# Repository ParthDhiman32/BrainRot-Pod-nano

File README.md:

# BrainRot-Pod-nano
BrainRot Pod Nano is an overengineered Embedded system project wth complex PCB and beautiful CAD enclosure mainly made for playing meme sounds and also can work as a mini music player   

# Motivation to create this and Outline of features
okay so this sounds like a really dumb project but the thing is this is a really good project infact this project will help me sharpen my PCB and CAD skills to a even newer level Because i will try my best to Make this project as polished as possible like i want to make this project as perfect as it could be 
I wanted to make a project to see what level are my skills are at.

My goals for this project are to mainly have a Beauitiful! PCB which is really pleasing to an engineers eyes and to also design an enclosure which encapsulates the beauty of the PCB while itself mantaining a really Smooth Sleek and Matte design 

This project will have a shitload of features ranging from a rotatory encoder to adjust the volume to a SD card module to load your songs to and even a AUX Jack because..WHY NOT!!! 

I want to mantain a sleek design like how apple iPODs used to be like and also make my own UI and UX for this project and Many tactile buttons for feedback maybe i'll even add a vibrating motor for haptic feedback

# Main Components Used:
1.  ESP32-S3-WROOM-1 Module 
2.  PCM5102A - Audio DAC
3.  MAX98357A - Audio Amplifer 
4.  TP4056 - Li-Po charger IC 
5.  DW01A - Battery Protection IC 
6.  FS83205A - Power Mosfet 
7.  ME6211 - LDO Regulator 
8.  AO3400 - BacLight Switch for TFT 
9.  1.54" SPI TFT display
10. Li-Po battery - 1100mAh 3.7V
11. Speaker - 3W 4Ω dynamic speaker
12. Rotary Encoder SMD
13. Tactile Buttons SMD 
14. USB C connector - 16 pin tactile receptacle 
15. Audio Jack - PJ-320A 3.5mm Stereo Audio Jack
16. SD Card slot - Push Pull SD card slot 
17. Battry connector - JST battery connector 
18. A lot of passive resistors 
19. A lot of passive capacitors 
20. M2 screws 

## Reason for selection of each part 
 1. ESP32-S3-WROOM-1 Module - this specific module was selected because it has 8MB of PSRAM which acts as the DMA audio buffer also because it has more than enough processing power and as it also has wifi and bluetooth i can add these features later to my project 

 2. PCM5102A - Normally audio DACs require bulky DC blocking Capacitors but as this IC has a negative voltage rail which produces ground centered Audio this eliminates the need of those bulky DC Blosking capacitors 

 3. MAX93857A - this is an Mono Class-D audio amplifer IC (amp for short) and it shares the common I2C bus as the DAC and also it will shut off automatically when the Audio jack / AUX will be connected 

 4. TP4056 - This is a very common Typical Li-Po battery chargin IC no need for more explanation

 5. DW01A - This is a battery protection IC which is paired with TP4056 which provides Short Circuit and overload protection to the battery 

 6. AP2112K-3.3 - This is a ultra low dropout power regulator meaning it will extract maximum voltage from the Lipo battery before it drops out it drops out around 3.55V unlike older inefficient AMS117 which dropout at around 4.3V

 7. ME6211 - efficiently converts the 5V from the power system to 3V3 volts the entire circuitry works on

 8. AO3400 - This is a simple PWM switch which will be used to control the intensity of Backlight of the 2.8" TFT Display 

 9.  1.54" SPI TFT display - Very high quality display with vivid range of colours and no grainy text 

 10. 1100mAh Li-Po battery provied long enough battery life that if optmized could give all day long runtime 
 
 11. 3W 4Ω dynamic speaker - Loud enough speaker and also can be driven Efficiently by our Audio amplifier circuitry 

 12. Rotary Encoder - To simply control the Volume 

 13. Tactile Buttons - Buttons with 5-20N of actuation force so that it gives a premium click! feel 

 14. USB C connector - for charging the battery and flashing / Updating the firmware 

 15. Audio Jack - Only to connect external wired earphones

 16. SD Card slot - Ti store Songs / MEME sounds 

 17. Battery Connector - A JST batter connector to prevent accidental rever polatiy connections 

 18. 19.  resistors and capacitors - Do i even need to explain why this is needed 

 20. M2 screws are small enough to be screwed and not be noticed easily

# PCB Schematics

## Complete Schematic

---

## Complete PCB

### Op-Amps & Audio Circuit

---

## Power System

---

## ESP32 & Peripheral Connections

# CAD DESIGN 

# BOM

| # | Component | Qty | Estimated Unit Cost | Estimated Total |
|---|---|---:|---:|---:|
| 1 | ESP32-S3-WROOM-1, 8MB PSRAM | 1 | $3.70 | $3.70 |
| 2 | PCM5102A Audio DAC | 1 | $1.25 | $1.25 |
| 3 | MAX98357A Class-D Audio Amplifier | 1 | $1.05 | $1.05 |
| 4 | TP4056 Li-Po Charger IC | 1 | $0.16 | $0.16 |
| 5 | DW01A Battery Protection IC | 1 | $0.11 | $0.11 |
| 6 | FS8205A / FS83205A Battery Protection MOSFET | 1 | $0.11 | $0.11 |
| 7 | ME6211 / AP2112K 3.3V LDO | 1 | $0.16 | $0.16 |
| 8 | AO3400 Backlight MOSFET | 1 | $0.08 | $0.08 |
| 9 | 1.54" SPI TFT Display | 1 | $2.63 | $2.63 |
| 10 | 3.7V 1100mAh Li-Po Battery | 1 | $3.15 | $3.15 |
| 11 | 3W 4Ω Dynamic Speaker | 1 | $1.05 | $1.05 |
| 12 | SMD Rotary Encoder | 1 | $0.42 | $0.42 |
| 13 | SMD Tactile Buttons | ~6 | $0.05 | $0.32 |
| 14 | USB-C 16-Pin Receptacle | 1 | $0.21 | $0.21 |
| 15 | PJ-320A 3.5mm Stereo Audio Jack | 1 | $0.21 | $0.21 |
| 16 | Push-Pull SD Card Socket | 1 | $0.42 | $0.42 |
| 17 | JST Battery Connector | 1 | $0.16 | $0.16 |
| 18 | Resistors | ~20–30 | — | $0.32 |
| 19 | Capacitors | ~20–30 | — | $0.63 |
| 20 | Misc. Diodes / LEDs / Small Components | — | — | $0.32 |
| 21 | M2 Screws + Mechanical Hardware | — | — | $0.53 |
| | **TOTAL ROUGH BOM ESTIMATE** | | | **≈ $17.01** |
| | **Recommended Budget Range** | | | **$17–$20** |

> **Note:** This is a rough prototype estimate. Actual prices may vary depending on the supplier, exact MPNs, quantity, shipping, and taxes. PCB manufacturing, assembly, and 3D-printing costs are **not included**.

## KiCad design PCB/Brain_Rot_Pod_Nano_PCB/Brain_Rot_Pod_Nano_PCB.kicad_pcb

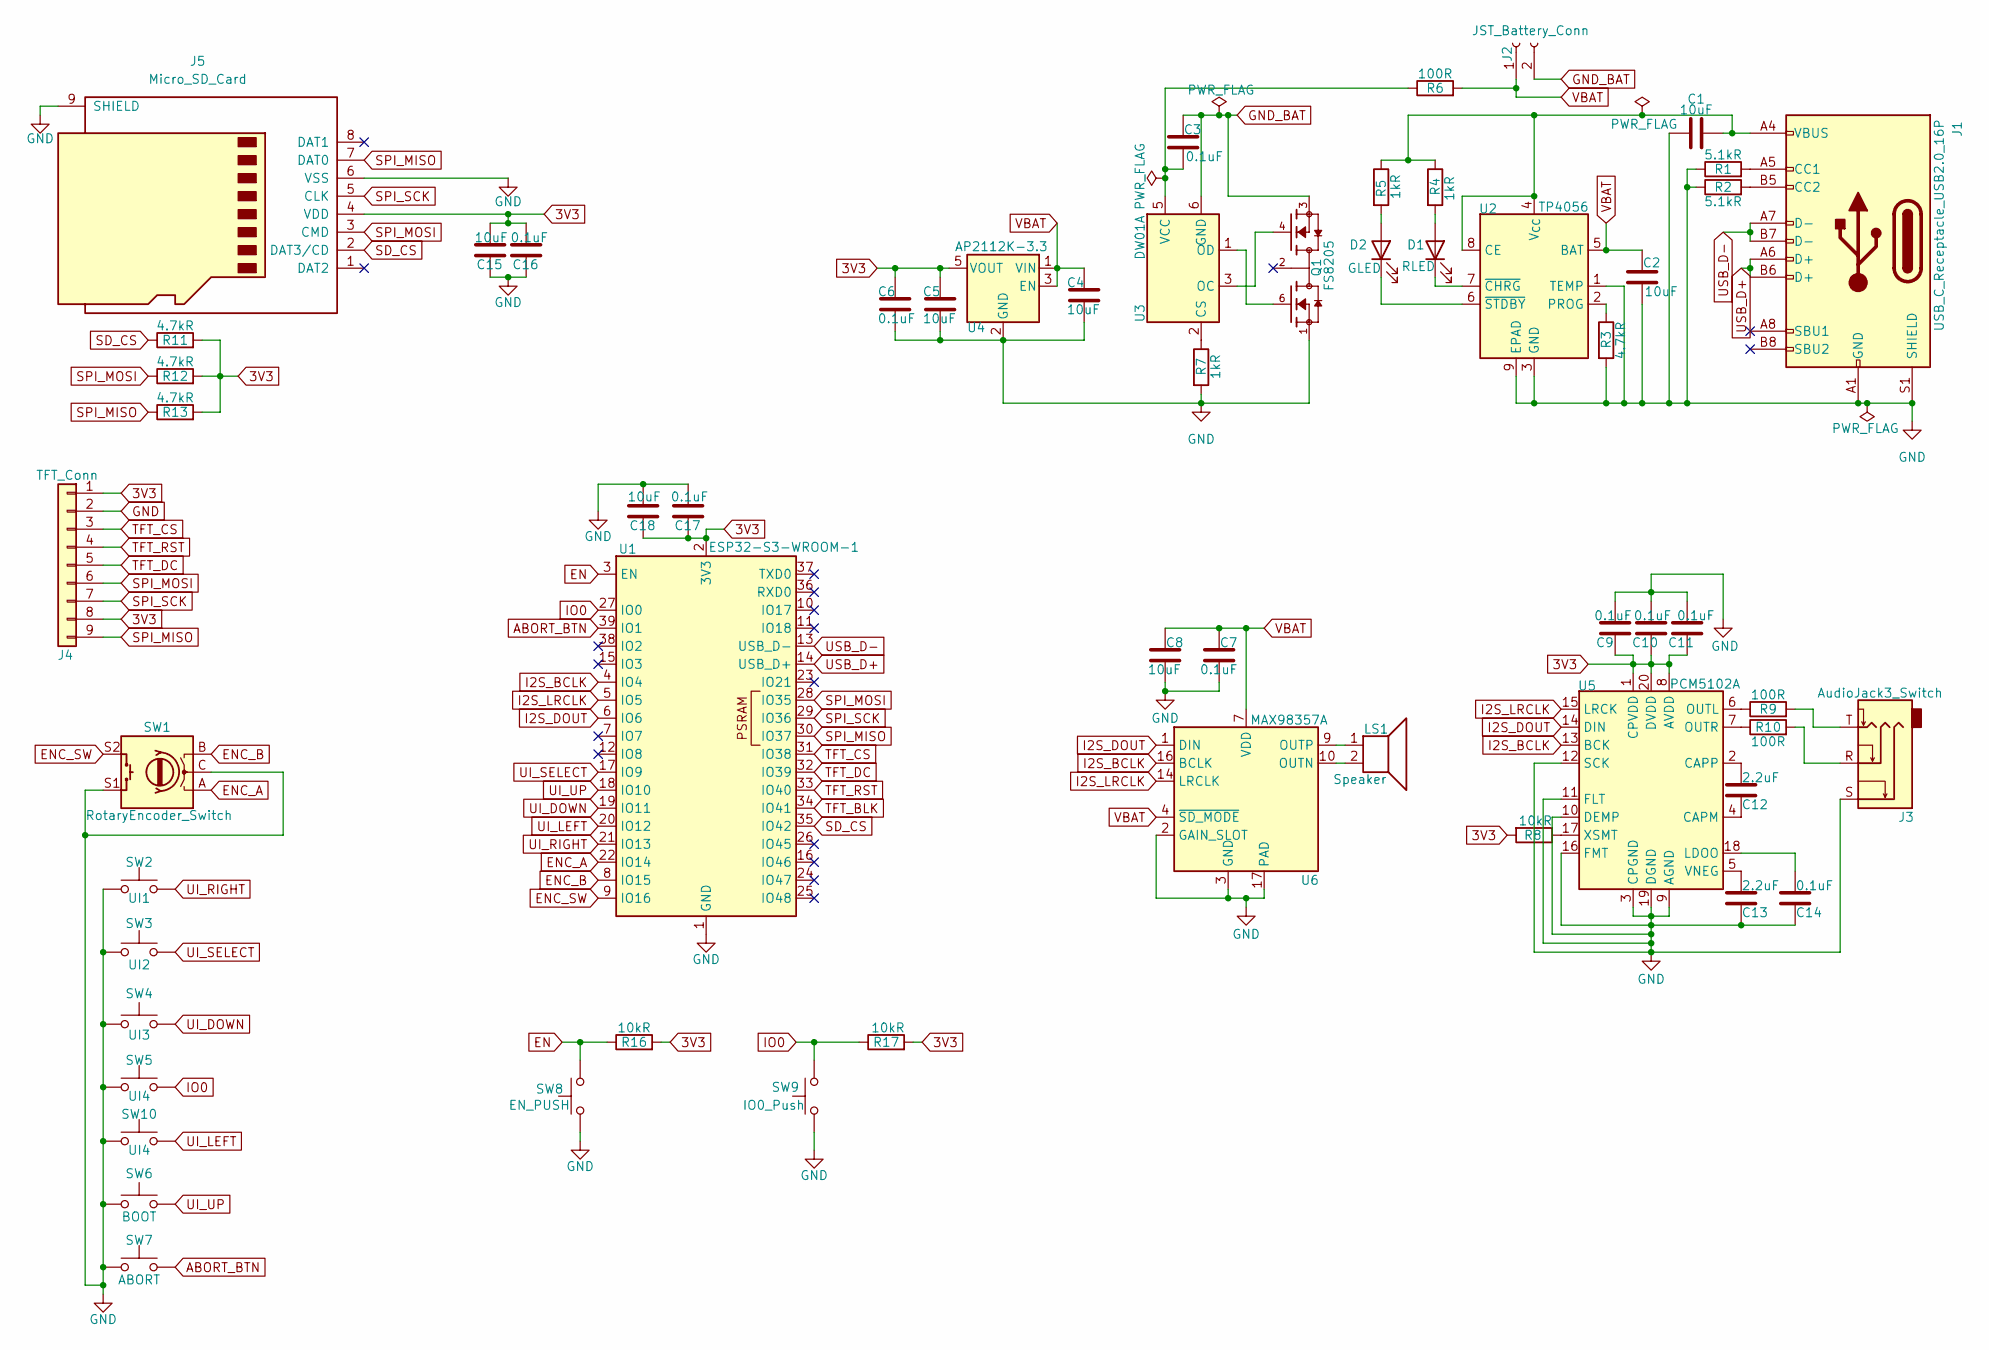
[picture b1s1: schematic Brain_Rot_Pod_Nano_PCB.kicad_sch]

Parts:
C1, C2, C4, C5, C8, C15, C18: 10uF; C_0805_2012Metric
C3, C6, C7, C9, C10, C11, C14, C16, C17: 0.1uF; C_0805_2012Metric
C12, C13: 2.2uF; C_0805_2012Metric
D1: RLED; LED_0805_2012Metric
D2: GLED; LED_0805_2012Metric
J1: USB_C_Receptacle_USB2.0_16P; USB_C_Receptacle_HRO_TYPE-C-31-M-12
J2: JST_Battery_Conn; JST_PH_S2B-PH-K_1x02_P2.00mm_Horizontal
J3: AudioJack3_Switch; Jack_3.5mm_CUI_SJ1-3523N_Horizontal
J4: TFT_Conn; PinHeader_1x09_P2.54mm_Vertical
J5: Micro_SD_Card; microSD_HC_Hirose_DM3AT-SF-PEJM5
LS1: Speaker; JST_PH_S2B-PH-K_1x02_P2.00mm_Horizontal
Q1: FS8205; TSSOP-8_4.4x3mm_P0.65mm; PARTREV 1.9
R1, R2: 5.1kR; R_0805_2012Metric
R3, R11, R12, R13: 4.7kR; R_0805_2012Metric
R4, R5, R7: 1kR; R_0805_2012Metric
R6, R9, R10: 100R; R_0805_2012Metric
R8, R16, R17: 10kR; R_0805_2012Metric
SW1: RotaryEncoder_Switch; RotaryEncoder_Alps_EC11E-Switch_Vertical_H20mm
SW2: UI1; SW_Cherry_MX_1.00u_PCB
SW3: UI2; SW_Cherry_MX_1.00u_PCB
SW4: UI3; SW_Cherry_MX_1.00u_PCB
SW5, SW10: UI4; SW_Cherry_MX_1.00u_PCB
SW6: BOOT; SW_Cherry_MX_1.00u_PCB
SW7: ABORT; SW_Cherry_MX_1.00u_PCB
SW8: EN_PUSH; SW_PUSH-12mm
SW9: IO0_Push; SW_PUSH-12mm
U1: ESP32-S3-WROOM-1
U2: TP4056; SOIC-8-1EP_3.9x4.9mm_P1.27mm_EP2.41x3.3mm_ThermalVias
U3: DW01A; SOT-23-6
U4: AP2112K-3.3; SOT-23-5
U5: PCM5102A; TSSOP-20_4.4x6.5mm_P0.65mm
U6: MAX98357A; TQFN-16-1EP_3x3mm_P0.5mm_EP1.23x1.23mm

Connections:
3V3: C5.1, C6.1, C9.2, C10.2, C11.2, C15.1, C16.1, C17.2, C18.2, J4.1, J4.8, J5.4 (VDD), R8.2, R11.2, R12.2, R13.2, R16.2, R17.2, U1.2 (3V3), U4.5 (VOUT), U5.1 (CPVDD), U5.8 (AVDD), U5.20 (DVDD)
ABORT_BTN: SW7.2, U1.39 (IO1)
EN: R16.1, SW8.2, U1.3 (EN)
ENC_A: SW1.A, U1.22 (IO14)
ENC_B: SW1.B, U1.8 (IO15)
ENC_SW: SW1.S2, U1.9 (IO16)
GND: C1.1, C2.1, C4.2, C5.2, C6.2, C7.2, C8.2, C9.1, C10.1, C11.1, C13.2, C14.2, C15.2, C16.2, C17.1, C18.1, J1.A1 (GND), J1.A12 (GND), J1.B1 (GND), J1.B12 (GND), J1.S1 (SHIELD), J3.S, J4.2, J5.6 (VSS), J5.9 (SHIELD), Q1.1, R1.1, R2.1, R3.2, R7.2, SW1.C, SW1.S1, SW2.1, SW3.1, SW4.1, SW5.1, SW6.1, SW7.1, SW8.1, SW9.1, SW10.1, U1.1 (GND), U1.40 (GND), U1.41 (GND), U2.1 (TEMP), U2.3 (GND), U2.9 (EPAD), U4.2 (GND), U5.3 (CPGND), U5.9 (AGND), U5.10 (DEMP), U5.11 (FLT), U5.12 (SCK), U5.16 (FMT), U5.19 (DGND), U6.2 (GAIN_SLOT), U6.3 (GND), U6.11 (GND), U6.15 (GND), U6.17 (PAD)
GND_BAT: C3.1, J2.2, Q1.3, U3.6 (GND)
I2S_BCLK: U1.4 (IO4), U5.13 (BCK), U6.16 (BCLK)
I2S_DOUT: U1.6 (IO6), U5.14 (DIN), U6.1 (DIN)
I2S_LRCLK: U1.5 (IO5), U5.15 (LRCK), U6.14 (LRCLK)
IO0: R17.1, SW5.2, SW9.2, U1.27 (IO0)
unnamed: D1.2 (A), R4.2
unnamed: D1.1 (K), U2.7 (~CHRG)
unnamed: D2.2 (A), R5.2
unnamed: D2.1 (K), U2.6 (~STDBY)
unnamed: J1.A5 (CC1), R1.2
unnamed: J1.B5 (CC2), R2.2
unnamed: J3.R, R10.2
unnamed: J3.T, R9.2
unnamed: C1.2, J1.A4 (VBUS), J1.A9 (VBUS), J1.B4 (VBUS), J1.B9 (VBUS), R4.1, R5.1, U2.4 (V_{CC}), U2.8 (CE)
unnamed: R3.1, U2.2 (PROG)
unnamed: R7.1, U3.2 (CS)
unnamed: Q1.4, U3.3 (OC)
unnamed: Q1.6, U3.1 (OD)
unnamed: C3.2, R6.1, U3.5 (VCC)
unnamed: C12.2, U5.4 (CAPM)
unnamed: C12.1, U5.2 (CAPP)
unnamed: C14.1, U5.18 (LDOO)
unnamed: R9.1, U5.6 (OUTL)
unnamed: R10.1, U5.7 (OUTR)
unnamed: C13.1, U5.5 (VNEG)
unnamed: R8.1, U5.17 (XSMT)
unnamed: LS1.2, U6.10 (OUTN)
unnamed: LS1.1, U6.9 (OUTP)
SD_CS: J5.2 (DAT3/CD), R11.1, U1.35 (IO42)
SPI_MISO: J4.9, J5.7 (DAT0), R13.1, U1.30 (IO37)
SPI_MOSI: J4.6, J5.3 (CMD), R12.1, U1.28 (IO35)
SPI_SCK: J4.7, J5.5 (CLK), U1.29 (IO36)
TFT_BLK: U1.34 (IO41)
TFT_CS: J4.3, U1.31 (IO38)
TFT_DC: J4.5, U1.32 (IO39)
TFT_RST: J4.4, U1.33 (IO40)
UI_DOWN: SW4.2, U1.19 (IO11)
UI_LEFT: SW10.2, U1.20 (IO12)
UI_RIGHT: SW2.2, U1.21 (IO13)
UI_SELECT: SW3.2, U1.17 (IO9)
UI_UP: SW6.2, U1.18 (IO10)
USB_D+: J1.A6 (D+), J1.B6 (D+), U1.14 (USB_D+)
USB_D-: J1.A7 (D-), J1.B7 (D-), U1.13 (USB_D-)
VBAT: C2.2, C4.1, C7.1, C8.1, J2.1, R6.2, U2.5 (BAT), U4.1 (VIN), U4.3 (EN), U6.4 (~SD_MODE), U6.7 (VDD), U6.8 (VDD)

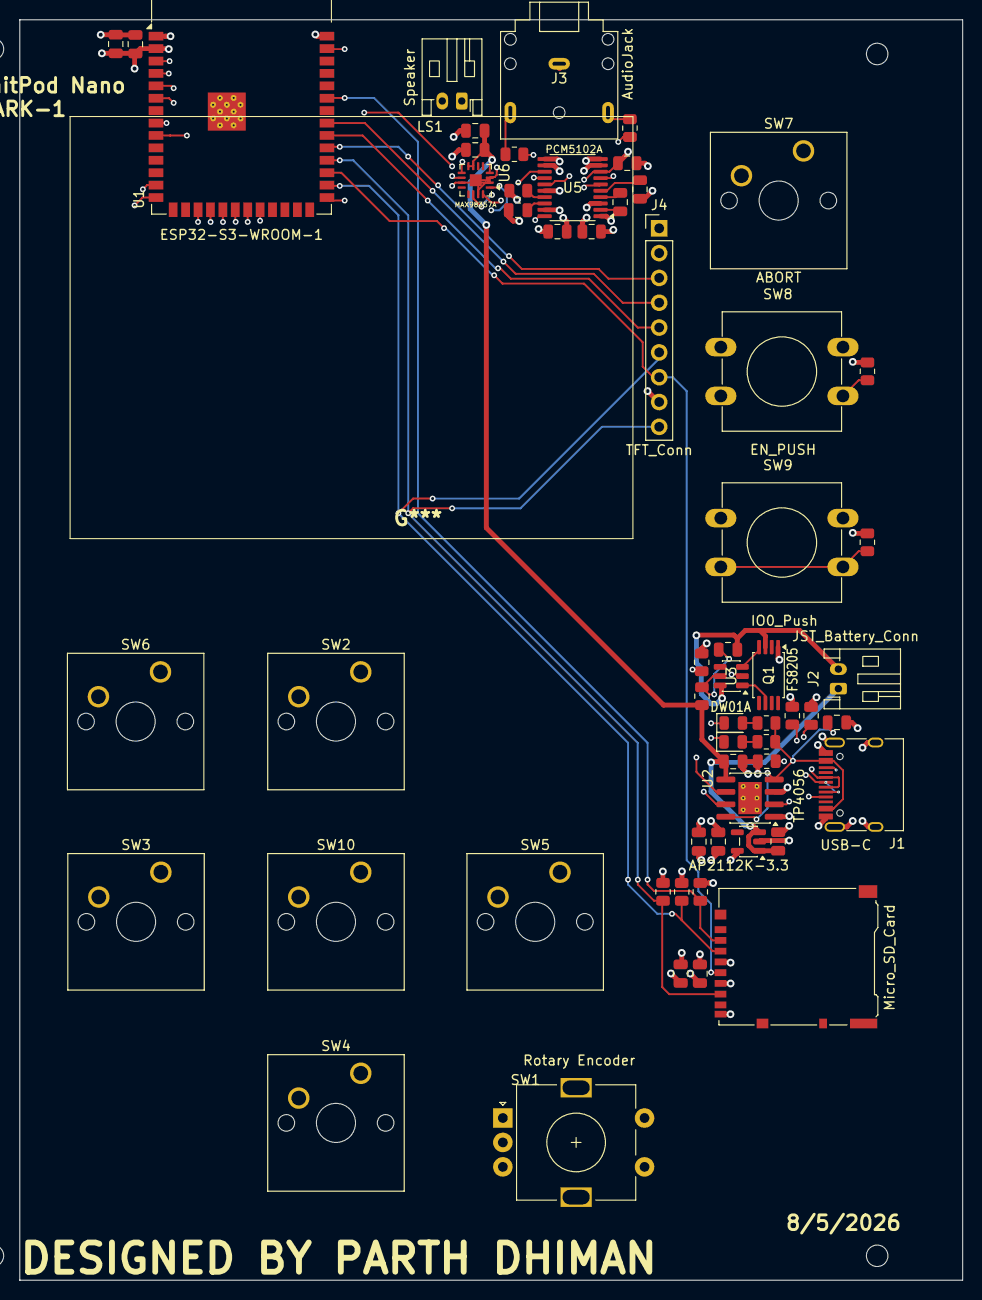
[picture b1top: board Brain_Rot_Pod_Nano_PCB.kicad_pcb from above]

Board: 6 copper layers, 96.5 x 129.0 mm, 58 parts (0 on the bottom side), 50 nets.

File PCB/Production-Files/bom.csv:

Designator,Footprint,Quantity,Value,LCSC Part #
"C1, C15, C18, C2, C4, C5, C8",0805,7,10uF,
"C10, C11, C14, C16, C17, C3, C6, C7, C9",0805,9,0.1uF,
"C12, C13",0805,2,2.2uF,
D1,0805,1,RLED,
D2,0805,1,GLED,
J1,USB_C_Receptacle_HRO_TYPE-C-31-M-12,1,USB-C,
J2,JST_PH_S2B-PH-K_1x02_P2.00mm_Horizontal,1,JST_Battery_Conn,
J3,Jack_3.5mm_CUI_SJ1-3523N_Horizontal,1,AudioJack,
J4,PinHeader_1x09_P2.54mm_Vertical,1,TFT_Conn,
J5,microSD_HC_Hirose_DM3AT-SF-PEJM5,1,Micro_SD_Card,
LS1,JST_PH_S2B-PH-K_1x02_P2.00mm_Horizontal,1,Speaker,
Q1,TSSOP-8_4.4x3mm_P0.65mm,1,FS8205,
"R1, R2",0805,2,5.1kR,
"R10, R6, R9",0805,3,100R,
"R11, R12, R13, R3",0805,4,4.7kR,
"R16, R17, R8",0805,3,10kR,
"R4, R5, R7",0805,3,1kR,
SW1,RotaryEncoder_Alps_EC11E-Switch_Vertical_H20mm,1,Rotary Encoder,
"SW10, SW5",SW_Cherry_MX_1.00u_PCB,2,UI4,
SW2,SW_Cherry_MX_1.00u_PCB,1,UI1,
SW3,SW_Cherry_MX_1.00u_PCB,1,UI2,
SW4,SW_Cherry_MX_1.00u_PCB,1,UI3,
SW6,SW_Cherry_MX_1.00u_PCB,1,BOOT,
SW7,SW_Cherry_MX_1.00u_PCB,1,ABORT,
SW8,SW_PUSH-12mm,1,EN_PUSH,
SW9,SW_PUSH-12mm,1,IO0_Push,
U1,ESP32-S3-WROOM-1,1,ESP32-S3-WROOM-1,
U2,SOIC-8-1EP_3.9x4.9mm_P1.27mm_EP2.41x3.3mm_ThermalVias,1,TP4056,
U3,SOT-23-6,1,DW01A,
U4,SOT-23-5,1,AP2112K-3.3,
U5,TSSOP-20_4.4x6.5mm_P0.65mm,1,PCM5102A,
U6,TQFN-16-1EP_3x3mm_P0.5mm_EP1.23x1.23mm,1,MAX98357A,

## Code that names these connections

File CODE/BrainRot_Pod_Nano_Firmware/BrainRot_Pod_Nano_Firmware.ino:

// Sample firmware for Brain_Rot_Pod_Nano
// Overengineered Firmware for Overengineered project

#include <SPI.h>
#include <SD.h>
#include <TFT_eSPI.h>
#include "AudioFileSourceSD.h"
#include "AudioGeneratorWAV.h"
#include "AudioOutputI2S.h"

#define I2S_BCLK       4
#define I2S_LRC        5
#define I2S_DOUT       6

#define SD_CS          42
#define SD_MOSI        35
#define SD_MISO        37
#define SD_CLK         36

#define ENC_A          14
#define ENC_B          15
#define ENC_SW         16

#define BTN_ABORT      1

enum SystemState {
  STATE_MENU,
  STATE_MUSIC_PLAYING,
  STATE_MEME_SETUP,
  STATE_MEME_ARMED,
  STATE_MEME_PLAYING
};

SystemState currentState = STATE_MENU;

AudioGeneratorWAV *wav;
AudioFileSourceSD *file;
AudioOutputI2S *out;

float currentVolume = 0.6;

uint32_t memeStartTime = 0;
uint32_t memeDelayMs = 60000;
bool memeArmed = false;

uint32_t lastButtonPress = 0;
int lastEncoderState = HIGH;

uint32_t lastUIUpdate = 0;
bool uiNeedsUpdate = true;

TFT_eSPI tft = TFT_eSPI();

void setup() {

  Serial.begin(115200);

  pinMode(ENC_A, INPUT_PULLUP);
  pinMode(ENC_B, INPUT_PULLUP);
  pinMode(ENC_SW, INPUT_PULLUP);

  pinMode(BTN_ABORT, INPUT_PULLUP);

  // Initialize TFT
  tft.init();
  tft.setRotation(1);
  tft.fillScreen(TFT_BLACK);
  tft.setTextColor(TFT_WHITE, TFT_BLACK);

  // Initialize SPI
  SPI.begin(SD_CLK, SD_MISO, SD_MOSI, SD_CS);

  // Initialize SD card
  if (!SD.begin(SD_CS, SPI, 40000000)) {

    tft.drawString("SD CARD FAILED", 10, 10, 2);

    while (1) {
      delay(100);
    }
  }

  // Initialize audio system
  audioLogger = &Serial;

  file = new AudioFileSourceSD();
  out = new AudioOutputI2S();
  wav = new AudioGeneratorWAV();

  // Configure I2S
  out->SetPinout(I2S_BCLK, I2S_LRC, I2S_DOUT);

  // Set initial volume
  out->SetGain(currentVolume);

  uiNeedsUpdate = true;
}


void loop() {

  handleInputs();
  handleAudio();
  handleMemeTimer();
  updateUI();

}


void handleAudio() {

  if (wav && wav->isRunning()) {

    if (!wav->loop()) {

      wav->stop();

      file->close();

      if (currentState == STATE_MEME_PLAYING) {

        currentState = STATE_MENU;
        uiNeedsUpdate = true;

      }
    }
  }
}


void playFile(const char *filename) {

  if (wav->isRunning()) {

    wav->stop();
    file->close();

  }

  if (!file->open(filename)) {

    Serial.print("Failed to open: ");
    Serial.println(filename);

    currentState = STATE_MENU;
    uiNeedsUpdate = true;

    return;
  }

  if (!wav->begin(file, out)) {

    Serial.println("Failed to start WAV playback");

    file->close();

    currentState = STATE_MENU;
    uiNeedsUpdate = true;

    return;
  }
}


void handleInputs() {

  uint32_t now = millis();

  // Button handling
  if (now - lastButtonPress > 50) {

    // Encoder push button
    if (digitalRead(ENC_SW) == LOW) {

      if (currentState == STATE_MUSIC_PLAYING) {

        // Mute / unmute audio
        if (wav->isRunning()) {

          if (currentVolume > 0.0) {
            out->SetGain(0.0);
          }
          else {
            out->SetGain(0.6);
          }

        }

      }

      else if (currentState == STATE_MEME_SETUP) {

        memeArmed = true;
        memeStartTime = now;

        currentState = STATE_MEME_ARMED;

        uiNeedsUpdate = true;

      }

      else if (currentState == STATE_MENU) {

        playFile("/music/song.wav");

        currentState = STATE_MUSIC_PLAYING;

        uiNeedsUpdate = true;

      }

      lastButtonPress = now;
    }


    // Abort button
    if (digitalRead(BTN_ABORT) == LOW) {

      if (wav->isRunning()) {
        wav->stop();
      }

      if (file) {
        file->close();
      }

      memeArmed = false;

      currentState = STATE_MENU;

      uiNeedsUpdate = true;

      lastButtonPress = now;
    }
  }


  // Rotary encoder
  int currentEncoderState = digitalRead(ENC_A);

  if (currentEncoderState != lastEncoderState &&
      currentEncoderState == LOW) {

    if (digitalRead(ENC_B) != currentEncoderState) {

      currentVolume += 0.05;

      if (currentVolume > 1.0) {
        currentVolume = 1.0;
      }

    }
    else {

      currentVolume -= 0.05;

      if (currentVolume < 0.0) {
        currentVolume = 0.0;
      }
    }

    out->SetGain(currentVolume);

    uiNeedsUpdate = true;
  }

  lastEncoderState = currentEncoderState;
}


void handleMemeTimer() {

  if (currentState == STATE_MEME_ARMED && memeArmed) {

    uint32_t now = millis();

    uint32_t elapsed = now - memeStartTime;


    // Update countdown once per second
    if (now - lastUIUpdate >= 1000) {

      uiNeedsUpdate = true;
      lastUIUpdate = now;

    }


    // Timer expired
    if (elapsed >= memeDelayMs) {

      memeArmed = false;

      currentState = STATE_MEME_PLAYING;

      uiNeedsUpdate = true;

      playFile("/memes/faaaah.wav");
    }
  }
}


void updateUI() {

  if (!uiNeedsUpdate) {
    return;
  }

  uiNeedsUpdate = false;

  tft.fillScreen(TFT_BLACK);


  switch (currentState) {

    case STATE_MENU:

      tft.drawString("BRAINROT POD NANO", 10, 10, 4);

      tft.drawString("> MUSIC", 10, 50, 2);

      tft.drawString("  MEME SETUP", 10, 70, 2);

      break;


    case STATE_MUSIC_PLAYING:

      tft.drawString("MUSIC PLAYING", 10, 10, 4);

      tft.drawString("> song.wav", 10, 50, 2);

      tft.drawString("Volume:", 10, 90, 2);

      tft.drawNumber(
        (int)(currentVolume * 100),
        80,
        90,
        2
      );

      break;


    case STATE_MEME_SETUP:

      tft.drawString("MEME SETUP", 10, 10, 4);

      tft.drawString("FAAAAAH.wav", 10, 50, 2);

      tft.drawString("Delay:", 10, 80, 2);

      tft.drawNumber(
        memeDelayMs / 1000,
        80,
        80,
        2
      );

      tft.drawString("SECONDS", 120, 80, 2);

      break;


    case STATE_MEME_ARMED: {

      tft.drawString("MEME TIMER", 10, 10, 4);

      tft.drawString("FAAAAAH.wav", 10, 40, 2);

      uint32_t elapsed = millis() - memeStartTime;

      uint32_t remainingMs = 0;

      if (elapsed < memeDelayMs) {
        remainingMs = memeDelayMs - elapsed;
      }

      uint32_t remaining = remainingMs / 1000;

      tft.drawString("T-MINUS:", 10, 80, 4);

      tft.drawNumber(
        remaining,
        120,
        80,
        4
      );

      break;
    }


    case STATE_MEME_PLAYING:

      tft.fillScreen(TFT_RED);

      tft.setTextColor(TFT_WHITE, TFT_RED);

      tft.drawString("💀", 40, 50, 4);
      tft.drawString("FAAAAAAH", 40, 100, 4);

      tft.setTextColor(TFT_WHITE, TFT_BLACK);

      break;
  }
}
